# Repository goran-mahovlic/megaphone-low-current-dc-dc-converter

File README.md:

# High-Efficiency Low-Current DC:DC Converter Module for MEGAphone

Adapted from Byte Sized Projects for MEGAphone
Used and released under GPLv3

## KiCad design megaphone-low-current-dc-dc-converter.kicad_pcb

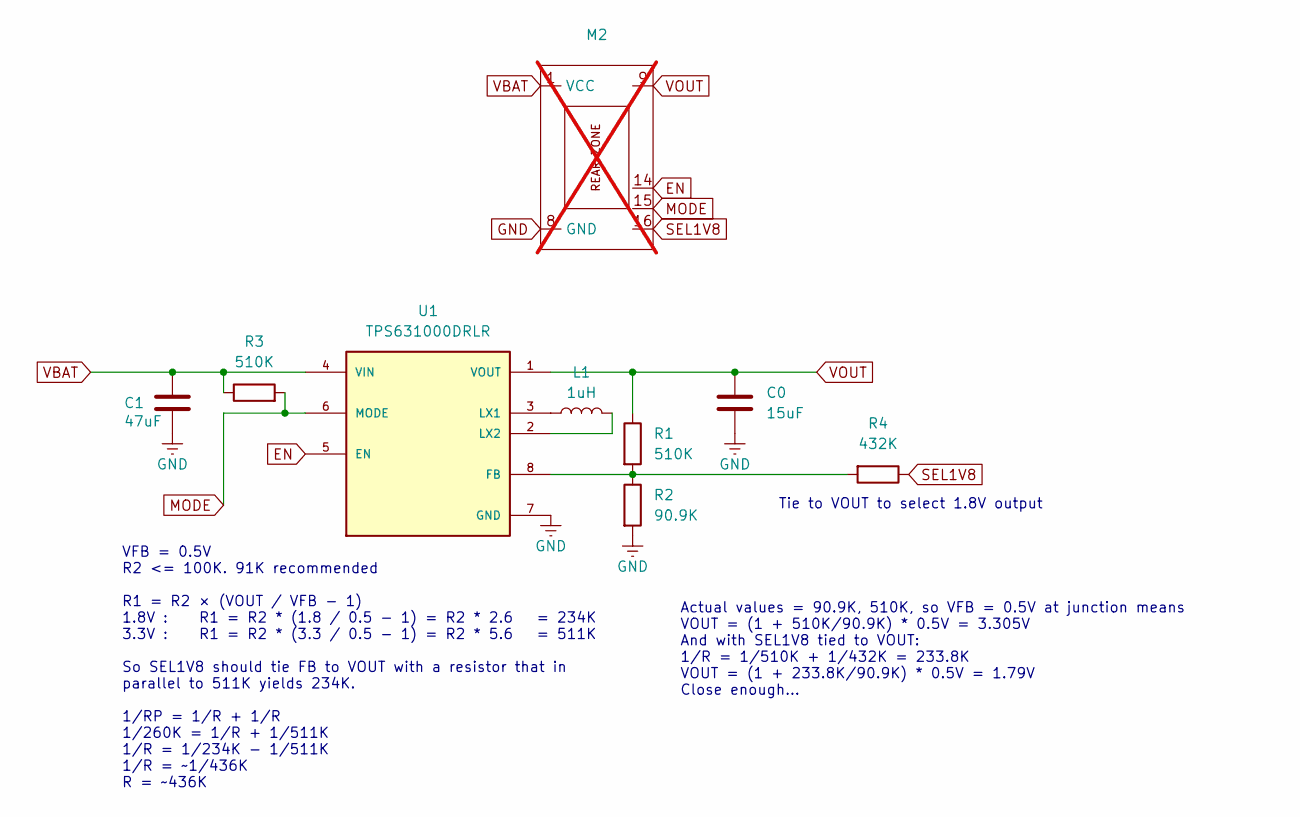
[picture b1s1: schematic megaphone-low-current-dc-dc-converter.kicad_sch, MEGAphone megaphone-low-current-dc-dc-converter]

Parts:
C0: 15uF; C_0805_2012Metric; LCSC C23692982
C1: 47uF; C_0805_2012Metric; LCSC C16780
L1: 1uH; L_1008_2520Metric_Pad1.43x2.20mm_HandSolder; LCSC C882955
M2: MegaCastle2x8-Module-I15.0x15.5-M8187-SPAREPAD; not fitted
R1, R3: 510K; R_0805_2012Metric; LCSC C2907332
R2: 90.9K; R_0805_2012Metric; LCSC C229044
R4: 432K; R_0805_2012Metric; LCSC C137526
U1: TPS631000DRLR; SOT50P160X60-8N; PARTREV B; LCSC C5219190

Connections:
EN: M2.14, U1.5 (EN)
GND: C0.2, C1.1, M2.8 (GND), R2.2, U1.7 (GND)
MODE: M2.15, R3.2, U1.6 (MODE)
unnamed: R1.2, R2.1, R4.2, U1.8 (FB)
unnamed: L1.1, U1.3 (LX1)
unnamed: L1.2, U1.2 (LX2)
SEL1V8: M2.16, R4.1
VBAT: C1.2, M2.1 (VCC), R3.1, U1.4 (VIN)
VOUT: C0.1, M2.9, R1.1, U1.1 (VOUT)

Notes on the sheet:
VFB = 0.5V R2 <= 100K. 91K recommended R1 = R2 × (VOUT / VFB - 1) 1.8V : R1 = R2 * (1.8 / 0.5 - 1) = R2 * 2.6 = 234K 3.3V : R1 = R2 * (3.3 / 0.5 - 1) = R2 * 5.6 = 511K So SEL1V8 should tie FB to VOUT with a resistor that in parallel to 511K yields 234K. 1/RP = 1/R + 1/R 1/260K = 1/R + 1/511K 1/R = 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
Actual values = 90.9K, 510K, so VFB = 0.5V at junction means VOUT = (1 + 510K/90.9K) * 0.5V = 3.305V And with SEL1V8 tied to VOUT: 1/R = 1/510K + 1/432K = 233.8K VOUT = (1 + 233.8K/90.9K) * 0.5V = 1.79V Close enough...
Tie to VOUT to select 1.8V output

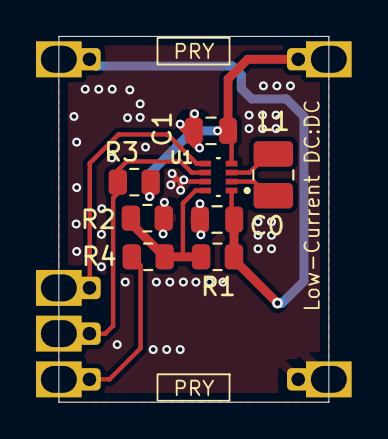
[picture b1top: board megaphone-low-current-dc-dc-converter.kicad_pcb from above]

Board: 2 copper layers, 15.0 x 20.3 mm, 9 parts (1 on the bottom side), 9 nets.

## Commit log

2025-02-22 begin refactoring MPPT controller to extract just DC:DC
2025-02-22 rename files for new project
2025-02-22 rename more files
2025-02-22 change all MPPT references in files to new project name
2025-02-22 prune out unnecessary part of schematic
2025-02-22 finish adapting MPPT into simple low-current 3.3V DC:DC regulator
2025-02-22 add footprint, symbol and 3D model for DC:DC regulator
2025-02-22 use TPS631000 DC:DC converter
2025-02-22 finish PCB layout
2025-08-05 Updating footprint, and re-routing
2025-08-07 Adding JLCPCB production files
